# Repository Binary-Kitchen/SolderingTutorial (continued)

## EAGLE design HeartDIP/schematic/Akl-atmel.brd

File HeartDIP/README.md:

# Heart - DIP
Small soldering kit with an heart on from https://wiki.blinkenarea.org/index.php/AntiKippenLights-Atmel

- Status: **Complete**
- Difficulty: **2/5**

### Parts List

| Menge | Name         | Beschreibung                       | Beschriftung/Farbcode                   |
|-------|--------------|------------------------------------|-----------------------------------------|
| 1     | C1           | Keramik Kondensator 100nF          | 104                                     |
| 1     | IC1          | Mikrocontroller Atmel ATTiny 2313A |                                         |
| 18    | LED1 - LED18 | LED 5mm                            |                                         |
| 6     | R1 - R6      | Widerstand 47 Ohm                  | Gelb - Violett - Schwarz - Gold - Braun |
| 1     | S1           | Taster                             |                                         |
| 1     | X1           | Klemme 2-polig                     |                                         |
| 1     |              | IC-Sockel 20-polig                 |                                         |
| 1     |              | Batteriehalter                     |                                         |
| 2     |              | Batterie Mignon (AA)               |                                         |
| 1     |              | Platine                            |                                         |

### Manual
You can find the manual and pictures of every step in the manual folder.

### Copyright and Authorship
The project is based on http://wiki.blinkenarea.org/index.php/AntiKippenLights-Mini

- Board: [CC-BY-NC-SA 4.0](https://creativecommons.org/licenses/by-nc-sa/4.0/) - Arne Rossius
- Manual (TeX): [LPPL](https://www.latex-project.org/lppl.txt) - [Marei Peischl](https://peitex.de)
- Manual (pdf): [CC-BY-SA 4.0](https://creativecommons.org/licenses/by-sa/4.0/) - [Binary Kitchen e.V.](https://www.binary-kitchen.de)

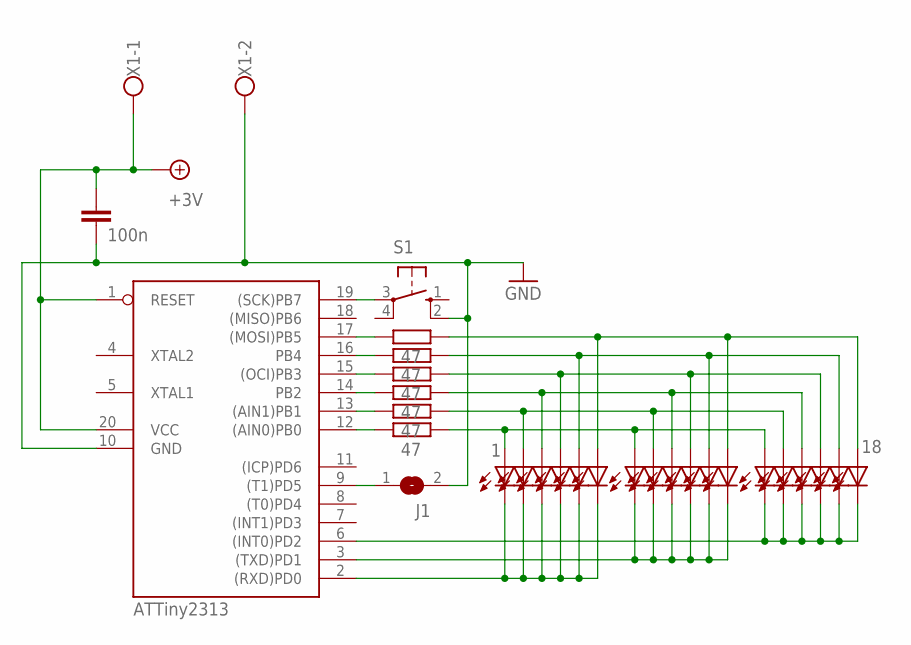
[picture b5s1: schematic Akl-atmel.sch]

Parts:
C1: 100n; C025-025X050
IC1: ATTiny2313; DIL20
J1: SJ
LED1: 1; LED5MM
LED2, LED3, LED4, LED5, LED6, LED7, LED8, LED9, LED10, LED11, LED12, LED13, LED14, LED15, LED16, LED17: LED5MM
LED18: 18; LED5MM
R1, R2, R3, R4, R5, R6: 47; 0207/7
S1: 10-XX; B3F-10XX
X1: CON2-RIA057; RIA_057_02

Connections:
+9V: C1.1, IC1.1 (RESET), IC1.20 (VCC), X1.1
GND: C1.2, IC1.10 (GND), J1.2, S1.2 (S1), X1.2
unnamed: IC1.17 ((MOSI)PB5), R1.1
unnamed: IC1.16 (PB4), R2.1
unnamed: IC1.15 ((OCI)PB3), R3.1
unnamed: IC1.14 (PB2), R4.1
unnamed: IC1.13 ((AIN1)PB1), R5.1
unnamed: IC1.12 ((AIN0)PB0), R6.1
unnamed: LED1.A, LED7.A, LED13.A, R6.2
unnamed: LED2.A, LED8.A, LED14.A, R5.2
unnamed: LED3.A, LED9.A, LED15.A, R4.2
unnamed: LED4.A, LED10.A, LED16.A, R3.2
unnamed: LED5.A, LED11.A, LED17.A, R2.2
unnamed: LED6.A, LED12.A, LED18.A, R1.2
unnamed: IC1.2 ((RXD)PD0), LED1.K (C), LED2.K (C), LED3.K (C), LED4.K (C), LED5.K (C), LED6.K (C)
unnamed: IC1.3 ((TXD)PD1), LED7.K (C), LED8.K (C), LED9.K (C), LED10.K (C), LED11.K (C), LED12.K (C)
unnamed: IC1.6 ((INT0)PD2), LED13.K (C), LED14.K (C), LED15.K (C), LED16.K (C), LED17.K (C), LED18.K (C)
unnamed: IC1.19 ((SCK)PB7), S1.3
unnamed: IC1.9 ((T1)PD5), J1.1

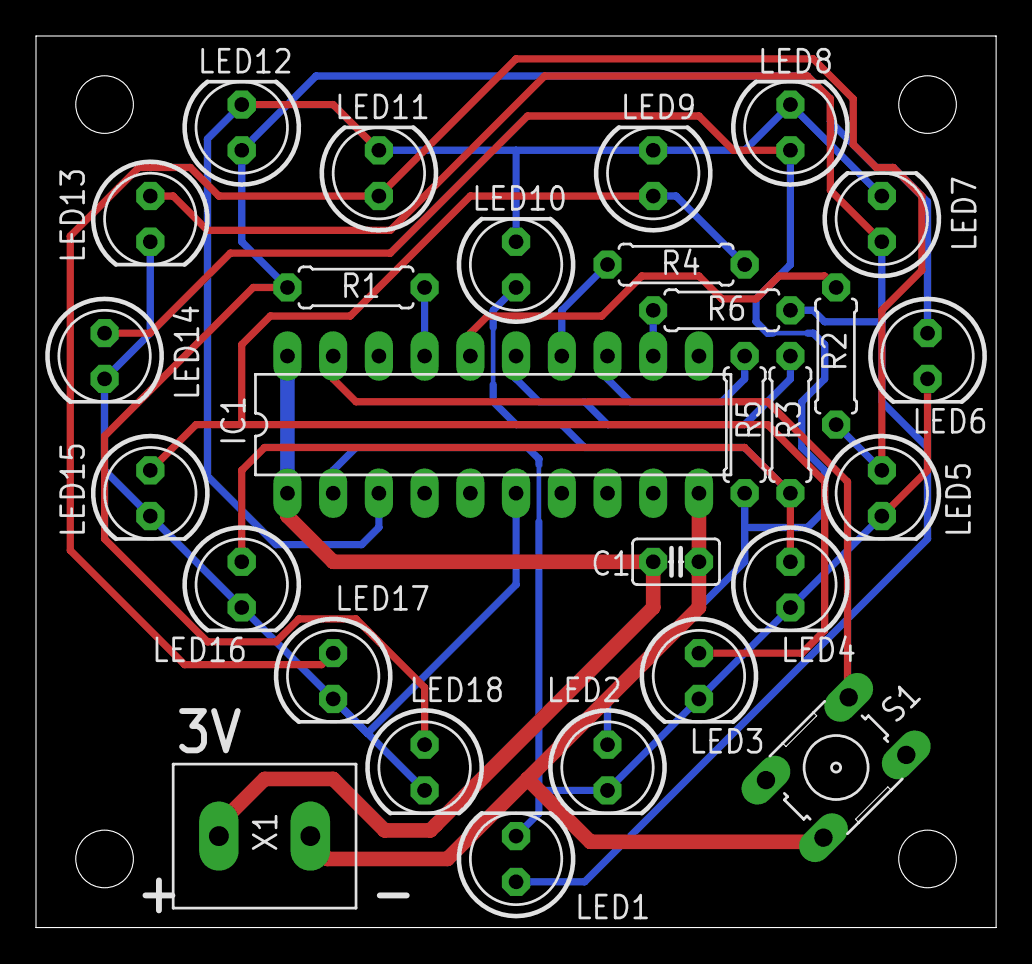
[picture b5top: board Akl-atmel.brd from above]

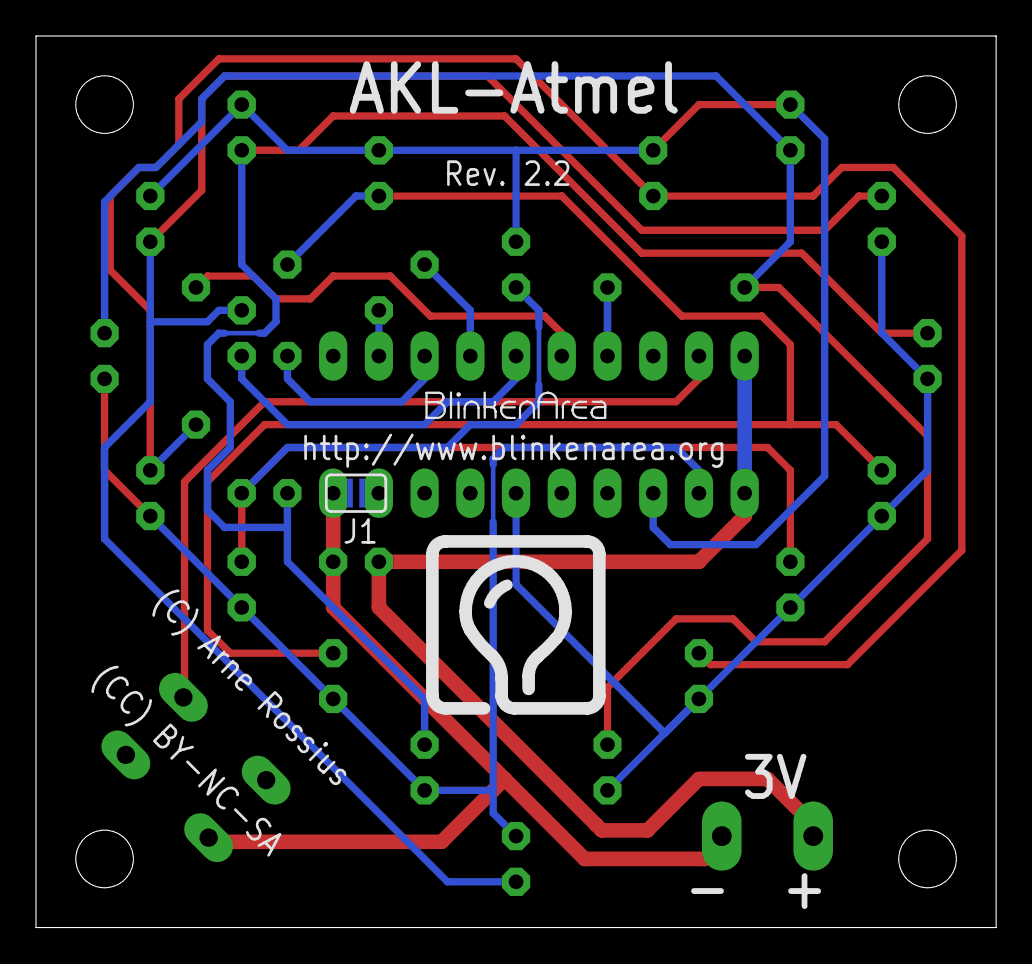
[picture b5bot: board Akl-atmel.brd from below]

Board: 2 copper layers, 53.3 x 49.5 mm, 31 parts (3 on the bottom side), 19 nets.

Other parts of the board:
U$2: LOGO_10MM_1
U$3: LOGO_10MM_2

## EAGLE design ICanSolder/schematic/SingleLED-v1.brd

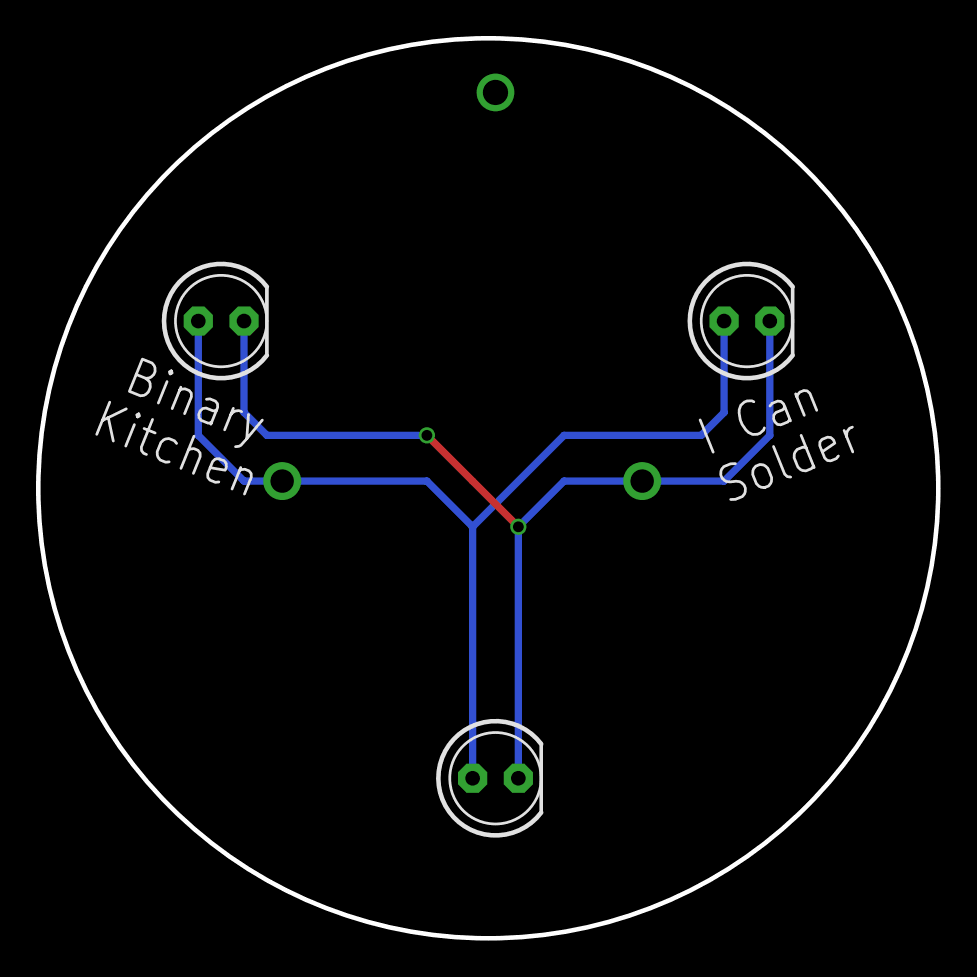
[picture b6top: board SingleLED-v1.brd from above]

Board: 2 copper layers, 50.0 x 50.0 mm, 4 parts (1 on the bottom side), 2 nets.

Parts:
G1: BATTCOM_20MM_PTH
LED1, LED2, LED3: LED5MM

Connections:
GND: G1.2, LED1.K, LED2.K, LED3.K
VCC: G1.1, LED1.A, LED2.A, LED3.A

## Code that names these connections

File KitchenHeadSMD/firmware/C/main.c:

/*
 * Kitchenkopf.c
 *
 * Created: 04.03.2017 00:47:04
 * Author : Thomas Basler
 */ 

#define F_CPU 1000000UL

#include <avr/io.h>
#include <avr/interrupt.h>
#include <avr/sleep.h>
#include <util/delay.h>

#define COUNT_ROW 3
#define COUNT_COL 7
#define COUNT_LED (COUNT_ROW * COUNT_COL)
volatile uint8_t Pixels[COUNT_ROW * COUNT_COL];
volatile uint8_t CurRow = 0;
volatile uint8_t Status = 0;

volatile uint8_t w1, w2, col;

#define BUTTON_PIN PB7

void LedsAllOff();
void PixelsAllSet(uint8_t val);

int main(void)
{
    // Set PD0 - PD6 as output
	DDRD |= _BV(PD0) | _BV(PD1) | _BV(PD2) | _BV(PD3) | _BV(PD4) | _BV(PD5) | _BV(PD6);

	// Set PB0 - PB2 as output
	DDRB |= _BV(PB0) | _BV(PB1) | _BV(PB2);

	// Set PB7 as input
	DDRB &= ~_BV(BUTTON_PIN);

	// Set Pull-Up for PB7
	PORTB |= _BV(BUTTON_PIN);

	// Disable Analog Comparator to reduce power consumption
	ACSR |= _BV(ACD);

	// Enable pin change interrupt
	GIMSK |= _BV(PCIE);

	// Enable pin change interrupt only on PB7
	PCMSK |= _BV(PCINT7);

	// Enable interrupts
	sei();

	// Set Sleep mode to power down and enable sleep
	set_sleep_mode(SLEEP_MODE_PWR_DOWN);
	sleep_enable();

	// Perform sleep
	Status = 0;
	sleep_cpu();

	// Perform Wakeup
	sleep_disable();

	// Set Timer0 prescaler to 64
	TCCR0B |= _BV(CS00) | _BV(CS01);

	// Set Timer0 Mode to CTC
	TCCR0A |= _BV(WGM01);

	// Set Timer output compare
	// 1000000Hz / 64 / 52 = 300Hz Timer CTC --> 100Hz for the whole image (3 rows)
	OCR0A = 52;

	// Enable interrupt on compare match
	TIMSK |= _BV(OCIE0A);

	while (1) 
    {
		PixelsAllSet(0);

		// Animation 1
		for (uint8_t c = 0; c < 2; c++) {
			for (uint8_t i = 0; i < COUNT_LED; i++) {
				Pixels[i] ^= _BV(0);
				_delay_ms(50);
			}
		}

		// Animation 2
		for (uint8_t c = 0; c < 20; c++) {
			for (uint8_t i = 0; i < COUNT_LED; i+=2) {
				Pixels[i] |= _BV(0);
			}
			_delay_ms(10);
			PixelsAllSet(0);
			for (uint8_t i = 1; i < COUNT_LED; i+=2) {
				Pixels[i] |= _BV(0);
			}
			_delay_ms(10);
		}

		// Animation 3
		for (uint8_t c = 0; c < 10; c++) {
			PixelsAllSet(0);
			_delay_ms(300);
			PixelsAllSet(1);
			_delay_ms(300);
		}
		
		// Animation 4
		PixelsAllSet(0);
		#define SNAKE_SIZE 5
		for (uint8_t c = 0; c < 5; c++) {
			for (uint8_t i = 0; i < COUNT_LED + SNAKE_SIZE; i++) {
				if (i < COUNT_LED) {
					Pixels[i] |= _BV(0);
				}
				else {
					Pixels[i - COUNT_LED] |= _BV(0);
				}
				if (i >= SNAKE_SIZE) {
					Pixels[i - SNAKE_SIZE] &= ~_BV(0);
					_delay_ms(100);
				}
			}
		}

		// Animation 5
		for (uint8_t c = 0; c < 20; c++) {
			for (uint8_t i = 0; i < COUNT_LED / 2; i++) {
				PixelsAllSet(0);
				Pixels[i] |= _BV(0);
				Pixels[i + COUNT_LED / 2] = _BV(0);
				_delay_ms(50);
			}
		}

		// Animation 6
		for (uint8_t c = 0; c < 20; c++) {
			for (uint8_t i = COUNT_LED / 2; i > 0; i--) {
				PixelsAllSet(0);
				Pixels[i] |= _BV(0);
				Pixels[i + COUNT_LED / 2] = _BV(0);
				_delay_ms(50);
			}
		}
    }
}

inline void LedsAllOff()
{
	// Turn all off
	PORTD &= ~(_BV(PD0) | _BV(PD1) | _BV(PD2) | _BV(PD3) | _BV(PD4) | _BV(PD5) | _BV(PD6));
	PORTB |= _BV(PB0) | _BV(PB1) | _BV(PB2);
}

void PixelsAllSet(uint8_t val)
{
	for (uint8_t i = 0; i < COUNT_LED; i++) {
		Pixels[i] = val;
	}
}

ISR(PCINT_vect)
{
	// Check if pin is high --> Button released
	if (bit_is_set(PINB, BUTTON_PIN)) {
		return;
	}
	
	if (Status) {
		// Current Status is on, so turn it off

		// Debounce button press
		for (w1 = 0; w1 < 0x10; w1++) {
			for (w2 = 0; w2 < 254; w2++) {
				if (bit_is_set(PINB, BUTTON_PIN)) {
					return;
				}
			}
		}
		
		// Debounce button release
		for (w1 = 0; w1 < 254; w1++) {
			loop_until_bit_is_set(PINB, BUTTON_PIN);
		}

		// Clear Pin change interrupt (which was set when key was released)
		EIFR &= ~_BV(PCIF);

		// Enable interrupts to wakeup again
		sei();

		// Turn all off
		LedsAllOff();

		// Set Sleep mode to power down and enable sleep
		set_sleep_mode(SLEEP_MODE_PWR_DOWN);
		sleep_enable();

		// Perform sleep
		Status = 0;
		sleep_cpu();
	} 
	else {
		// Current Status is off, so turn it on

		// Perform Wakeup
		Status = 1;
		sleep_disable();
	}
}

ISR(TIMER0_COMPA_vect)
{
	// Turn all off
	LedsAllOff();

	// Activate current row
	PORTB &= ~_BV(CurRow);

	// Set Pixels of current row
	for (col = 0; col < COUNT_COL; col++) {
		if (Pixels[CurRow * COUNT_COL + col] & 1) {
			PORTD |= _BV(col);
		}
	}

	// Switch to next row
	CurRow++;
	if (CurRow >= COUNT_ROW) {
		CurRow = 0;
	}
}

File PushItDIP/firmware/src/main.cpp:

/*
 * main.cpp
 *
 * Copyright (c) Thomas Basler, 2018
 *
 * Authors:
 *   Thomas Basler <thomas@familie-basler.net>
 *
 * This work is licensed under the terms of the GNU GPL, version 3.  See
 * the LICENSE file in the top-level directory.
 */

#include <avr/wdt.h>
#include "SevenSegment.h"
#include "ModeHandler.h"
#include "AudioEngine.h"
#include "LedEngine.h"
#include "GameEngine.h"
#include "GameData.h"
#include "Bounce2.h"
#include "Configuration.h"
#include "SerialProtocol.h"

// Pin definitions
#define SEVEN_SEGMENT_CLK_PIN  15
#define SEVEN_SEGMENT_DATA_PIN 14
#define SEVEN_SEGMENT_STO_PIN  16
#define BUZZER_PIN             10
#define LED_YELLOW_PIN         2
#define LED_RED_PIN            3
#define LED_GREEN_PIN          4
#define LED_BLUE_PIN           5
#define BTN_YELLOW_PIN         6
#define BTN_RED_PIN            7
#define BTN_GREEN_PIN          8
#define BTN_BLUE_PIN           9
#define BTN_MODE_PIN           19
#define BTN_START_PIN          17
#define BTN_REPEAT_PIN         18

// Button position in BTN_PINS array
#define BTN_YELLOW 0
#define BTN_RED    1
#define BTN_GREEN  2
#define BTN_BLUE   3
#define BTN_MODE   4
#define BTN_START  5
#define BTN_REPEAT 6

const uint8_t btnPins[] = {
	BTN_YELLOW_PIN,
	BTN_RED_PIN,
	BTN_GREEN_PIN,
	BTN_BLUE_PIN,
	BTN_MODE_PIN,
	BTN_START_PIN,
	BTN_REPEAT_PIN
};

GameEngine game;
Bounce *buttons = new Bounce[sizeof(btnPins)];

void setup() {
	// Reset watchdog (must happen within the first few ticks)
	MCUSR = 0;
	wdt_disable();

	// Initialize 7 segment display
	SevenSegment.begin(
		SEVEN_SEGMENT_CLK_PIN, SEVEN_SEGMENT_DATA_PIN, SEVEN_SEGMENT_STO_PIN);
	SevenSegment.blank();
	Mode.begin();
	GameData.begin();
	SerialProtocol.begin();

	// Initialize LED pins
	Led.begin(
		LED_YELLOW_PIN, LED_RED_PIN,
		LED_GREEN_PIN, LED_BLUE_PIN);

	// Initialize buzzer
	Audio.begin(BUZZER_PIN);

	// Initialize button debouncing
	for (uint8_t btn = 0; btn < sizeof(btnPins); btn++) {
		buttons[btn].attach(btnPins[btn], INPUT_PULLUP);
		buttons[btn].interval(25);
	}

	// Initialize configuration
	Configuration.begin();

	// Initialize game engine
	game.begin();

	// Enable Pin change interrupt (required to wakeup after sleep)
	*digitalPinToPCMSK(BTN_START_PIN) |= _BV(digitalPinToPCMSKbit(BTN_START_PIN));
	PCICR |= _BV(digitalPinToPCICRbit(BTN_START_PIN));

	// Enable the watchdog
	wdt_enable(WDTO_60MS);
}

void loop() {

	wdt_reset();

	// Update button state
	// Handles debouncing and send button event to game engine
	for (uint8_t btn = 0; btn < sizeof(btnPins); btn++) {
		buttons[btn].update();

		if (buttons[btn].fell()) {
			switch (btn) {
			case BTN_YELLOW: game.sendEvent(IGameEngine::Event::BtnYellow); break;
			case BTN_RED: game.sendEvent(IGameEngine::Event::BtnRed); break;
			case BTN_GREEN: game.sendEvent(IGameEngine::Event::BtnGreen); break;
			case BTN_BLUE: game.sendEvent(IGameEngine::Event::BtnBlue); break;
			case BTN_MODE: game.sendEvent(IGameEngine::Event::BtnMode); break;
			case BTN_START: game.sendEvent(IGameEngine::Event::BtnStart); break;
			case BTN_REPEAT: game.sendEvent(IGameEngine::Event::BtnRepeat); break;
			}
		}
	}

	// Update AudioEngine
	Audio.update();

	// Update GameEngine
	game.sendEvent(GameEngine::Event::Tick);
	game.update();
}

ISR(PCINT1_vect)
{
}

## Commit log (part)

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2018-12-04 added new picture
2018-12-04 added board layout to manual
2018-12-04 adjusted board layout size
2018-12-04 recompiled manuals with new information
2018-12-13 added duration for pdfs
2018-12-13 added duration for labels and removed board and description version
2018-12-13 added 2--4 hours duration for atx breakoutboard
2018-12-13 added 1--2 hours duration for arrow smd
2018-12-13 added 1--2 hours duration for diceDIP
2018-12-13 added 1--2 hours duration for diceMcDIP
2018-12-13 added 1--2 hours duration for HeartDIP
2018-12-13 added 1--2 hours duration for KitchenHeadSMD
2018-12-13 added 20--40 minutes duration for NibblePeg
2018-12-13 added 20--40 minutes duration for NibblePegSwitch
2018-12-13 fixed an error with too wide headlines
2019-01-04 Add French translation for NibblePegDIPSwitch tutorial
2019-02-13 added first draft of the nibble++ description
2019-02-13 added readme
2019-04-19 Update README.md
    fix typo
    update resistor values
2019-08-11 Fixed resistor value
2019-08-13 exchanged box with boxes.py-box and updated svg
2019-08-13 updated parts-list to 7 box elements
2019-08-21 changed english step-file to represent new box. Simplified steps
2019-08-23 fixed description and added new pictures. Simplified manual
2019-08-23 fixed error
2019-08-23 updated pdf
2019-08-23 fixed errors and updated version
2019-11-06 sorted by alphabetic order
2019-11-06 added manual for I Can Solder
2019-11-06 added german translation for NibblePeg-Poster
2019-11-06 added picture
2019-11-06 fixed some error
2019-11-09 added Shitty Robots project
2019-11-09 display image license in manual
2019-11-12 use images without text where possible; additional german versions for the rest
2019-11-12 creative part should be part of manual
2019-11-13 fixing error and adding picture
2019-11-15 Refine nibble peg manuals.
2019-11-15 Edit readme.
2019-12-14 minor change from zaesa
2019-12-15 PushItDIP: Added first version of README.md
2019-12-15 PushItDIP: Added schematic
2019-12-15 PushItDIP: Added first version of pre developed source
2019-12-15 PushItDIP: Added first part of the manual
2019-12-15 PushItDIP: Fixed compiler warnings
2019-12-15 PushItDIP: Fixed several compiler warnings
2019-12-15 PushItDIP: Added .editorconfig
2019-12-15 PushItDIP: Fix several compiler warnings
2019-12-15 PushItDIP: Fixed compiler warning
2019-12-15 PushItDIP: Add settings.json to .gitignore
2019-12-15 PushItDIP: Changed board version to 1.1
    Changed position of texts for the multiplayer connector
2019-12-15 PushItDIP: Added parts and image to README.md
2019-12-15 PushItDIP: Fixed initialization issue with random number generator
2019-12-15 PushItDIP: Added cam job and gerber files for JLCPCB
2019-12-15 PushItDIP: Set the right fuses using PlatformIO
2019-12-15 PushItDIP: Erase when writing fuses
2019-12-15 PushItDIP: Fixed wrong part count
2019-12-15 PushItDIP: Enable watchdog and changed pin numbers from analog to digital
2019-12-15 PushItDIP: Moved Kitchen logo to layer tStop
2019-12-15 PushItDIP: Corrected naming of 7segement display
    Its called LED7 instead of LED5
2019-12-15 PushItDIP: Renamed SP1 to SG1 within the manuals (to match schematic)
2019-12-15 PushItDIP: First version of building steps
2019-12-15 PushItDIP: Added manual to use sticky tape in final stages
2019-12-21 PushItDIP: Migrated setting of fuses from python file to platformio.ini
2019-12-21 PushItDIP: Added some delay in multiplayer gameplay
2019-12-21 PushItDIP: Added simple compilation manual
2019-12-21 PushItDIP: Added additional hint regarding capacitors
2019-12-22 PushItDIP: Changed status from Development to Complete
2019-12-22 PushItDIP: Add to main README.md
2019-12-25 New translated files for Esperanto version
2019-12-25 New translated files for Espranto version
2019-12-25 Esperanto translation
2019-12-26 Plenk taken out.
2019-12-28 Update README.md
    Andere Widerstände im Päckchen
2020-01-08 changed picture
2020-05-06 add landing page and interactive board views
    add landing page with links to manuals and interactive board views. The
    landing page is automatically generated from the filesystem structure.
    Place a tumbnail.[jpg, jpeg, png, gif] inside the images folder and
    optionaly an ibom.html at the root folder of the project to generate
    output for it. The interactive board views can be generated with the
    kicad plugin "InteractiveHTMlBom" [https://github.com/openscopeproject/InteractiveHtmlBom]
2020-05-06 add interactive board for nibble++
2020-05-07 README: update to include link to landing page
2020-09-02 fixed latex error due to deprecated functions
2020-09-20 generated new index.html
2020-09-20 deleted schematics, updated readme and created new bom
2020-12-05 added video
2020-12-05 fixed overview-index
2020-12-05 minor changes
2020-12-05 fixed colour code
2021-01-06 added english and german manual for humo
2021-02-07 resized images and created new pdf
2021-02-07 created new pdf
2021-02-16 fixed readme
2021-02-17 updated index.html
2021-02-21 fixed some errors
2021-02-21 added cat in a box
2021-03-03 resistor color reference
2021-03-03 complete resistor_color_ref
2021-03-03 rebase part reference
2021-05-04 deleted not needed file
2021-05-04 fixed a error in parts list
2021-05-27 added 4-digit resistor naming scheme to ATXBreakoutBoardSMD
2021-08-17 added new I can solder description
2021-08-19 updated interactive board for I can solder
2021-08-19 fixed some errors in the description
2021-08-19 added english translation
2021-08-19 added resistor colorcode to manual
2021-08-19 added resistor colours to the manual
2021-08-19 added english translation for arrow soldering kit. fixing #46
2021-08-20 added translation
2021-08-20 fixed typo
2021-08-31 fixed csv-error
2021-08-31 resized unicorn pictures
2021-08-31 added rainbow butterfly
2021-09-13 Updated ATX Manual fixes https://github.com/Binary-Kitchen/SolderingTutorial/issues/48
2021-10-23 added mooncat
2021-10-23 added moon cat
2021-10-23 fixed some issues
2021-10-23 added youtube link
2021-10-24 fixed url
2021-10-24 added german translation and fixed typo
2021-10-29 Added cat02
2021-10-30 make ce, weee, an rohs possible
2021-10-30 added warnings to config
2021-10-30 delted wrong file
2021-10-30 compiled new pdfs
2021-10-30 renamed file
2021-12-06 added ermer beeper to index/readme
2021-12-08 added owl thief to soldering tutorial
2022-01-28 fixed optional terminal connector
2022-03-28 changed some parts
2022-08-03 added axolotl
2022-08-03 added rocket
2022-08-03 added rocket and axo
2022-08-06 added Katie
2022-08-06 updated index
2022-08-08 deleted not needed files
2022-08-31 changed layout to better determine between interactive board and manual
2022-08-31 generated new pdf
2022-09-04 changed steps in the manual due to customer feedback
2022-09-04 added legal stuff to the labels
2022-09-16 mirrored led-description due to feedback of @davedarko
2022-10-24 README.md: fixed some mistakes
2022-10-24 more fixes for the respective READMEs
2022-10-24 added press-entry
2022-10-24 changes due to Franziskas feedback
2022-11-05 feat: added mention to the case in README
2022-11-06 inclueded nets and tracks in ibom
2022-11-06 added tracks
2022-11-25 refined description for atx breakoutboard
2022-11-27 added Dino to soldering tutorial
2022-11-27 a litte larger pictures
2022-11-27 added correct link
2022-11-27 removed unused files
2022-12-15 changed 4-ring colour code to 5-ring colour code
2023-01-14 added NE555 Heart
2023-01-14 updated readme and index
2023-02-26 added NE555 Heart DIP
2023-02-26 fixed a minor typo
2023-04-02 added openDTU Breakout Board
2023-04-05 added pinecil case
2023-04-11 fixed some errors in daisy manual
2023-04-14 fixed some errors in pinecil case
2023-04-21 added and fixed some parts
2023-04-23 fixed an minor error
2023-05-13 added display SH1106
2023-05-23 fixed wrong part
2023-06-08 added CMT variation to openDTU breakoutboard
2023-06-27 added update option in last step
2023-07-15 updated correct .bin-file
2023-07-17 fixed small bugs
2023-07-17 fixed link
2023-07-17 added ibom
2023-07-17 added configuration and generated pdf
2023-07-17 added Al Hacka Alpaca to readme
2023-07-17 generated new index with al hacka alpaca
2023-08-27 Add A5 Nibbleklammer Booklet
2023-09-01 fixed cat in a box 2
2023-09-17 added new tip for thumb screws
2023-09-26 OpenDTU_Breakout: Typo fixes in de_steps.csv
2023-11-28 moved files due to error in index-creation script
2023-11-28 added robo robin
2023-11-28 updated pdfs
2023-12-16 updated opendtu manual to 390 ohm resistors
2024-01-22 updated parts-list for ring-light
2024-02-26 updated warning page for humo-manual
2024-03-31 Make make clean work when nothing has been built yet
    Also don't delete index.html
2024-05-30 updated config and resistor values
2024-05-30 added pictures for new spool
2024-05-30 edited new board version
2024-06-04 added CE-Certificates to a special manual. temporaray needed
2024-06-11 added Ebyte CMT legacy manual
2024-07-02 Update de_steps.csv
    typos and clarifications
2024-07-02 Update en_steps.csv
    typos and clarifications
2024-11-30 updated code to be more robust
2024-11-30 added elefant and bug
2024-12-01 Added SmartLED Instructions
2024-12-02 updated index and readme
2024-12-02 removed wrong pdfs
2024-12-02 reduced Image size and difficulty Level for SmartLED
2024-12-06 fixed wrong 47 ohm resistor
2024-12-07 Update README.md
    Schreibweise von Jugend hackt aktuallisiert
2024-12-21 added bleepbot
2024-12-22 added SolderBox
2025-01-05 fixed typo in German Humo Instruction
2025-01-14 updated manual - parts were wrong
2025-01-22 changed 82ohm to 100ohm
2025-02-06 added manual for b-good heart
2025-02-11 new difficulty and minor changes
2025-02-11 added brass wool cover
2025-02-11 updated pictures and description
2025-03-13 updated buylink
2025-06-13 add Mario to Manuals
2025-06-16 add Draussenfuchs Manual
2025-06-16 add 50Ohm Dummy load instructions
2025-06-25 added solarpunk synth
2025-06-25 added some buy links
2025-06-25 added blinkenrocket
2025-07-07 added english humo manual
2025-07-18 Humo (German manual): spelling and grammar fixes
2025-07-26 added motorboerd
2025-07-26 fixed jpg to png
2025-08-20 fixed 9 to 10 wooden parts
2025-09-06 replaced wrong ibom for 50ohm dummy load. fixed #65
2025-09-14 Improve wording
2025-09-16 updated manual parts list for diceDIP
2025-09-16 updated manual for humo to add hint for plastic rip mentioned in #67
2025-09-16 deleted optional for cable in partslist humo
2025-09-22 added mouse manula
2025-09-22 updated readme and ibom
2025-09-22 updated main readme
2025-09-24 updated warnings for unicorn
2025-09-24 updated version number and licence
2025-10-01 added NE555HeartTHT b-ware
2025-10-13 updated manual to v1.4.
2025-10-18 updated qr-code and fixed url
2025-11-04 fixed error in parts list
2025-11-04 Fixed typos and a link in README
    Fixed multiple typos in the README and updated an incorrect website link.
2025-11-04 Fixed typos in README.md
    Fixed some typos in the README
2025-11-04 Fixed typos in README
    Fixed some typos in README
2025-11-04 Fix typos and descriptions in parts list
    Fixed three typos and the descriptions in the parts list.
2025-11-12 BlinkyTree_Manual v1
2025-11-18 Fix Issue with Resistor Colors, preventing the build
2025-11-24 updated blinkytree
2025-12-13 minor changes in description for humo
2025-12-20 updated manual for new speaker
2026-01-21 renamed catinabox to pooping cat
2026-01-21 updated humo parts list
2026-01-26 minor changes.
2026-02-18 added new heartbeat soldering kit
2026-02-26 fixed wrond pdf link for humo
2026-03-04 renamed cat01 to SMDCat
2026-04-05 fixed broken links
2026-05-01 Adding mushroom rocket
2026-05-01 updating mushroomrocket
2026-05-01 Add Mushroom rocket to readme
2026-05-09 Add Shrocket soldering kit manual
2026-05-09 Update landing page with shrocket
2026-05-09 reduce file size of thumbnail images
2026-05-10 adding copy of blinkyparts.pretty instead of submodule to shrocket
